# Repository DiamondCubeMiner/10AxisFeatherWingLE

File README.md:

# 10AxisFeatherWingLE #
A 10-DOF Featherwing, powered by LSM9DS1 and BMP280.

## Description ##
This featherwing uses I2C to connect both the IMU (LSM9DS1) and the altimeter (BMP280) to the Feather.
I made this to design projects that require a 10-DOF IMU in a tiny package where breakouts can affect the weight a lot and may not be a good option, such as a quadcopter, a model plane, or a model rocket.

## Drivers ##
These drivers should work as the project is a derivative of SparkFun hardware:
  - [SparkFun_LSM9DS1_Arduino_Library](https://github.com/sparkfun/SparkFun_LSM9DS1_Arduino_Library)
  - [SparkFun_BME280_Arduino_Library](https://github.com/sparkfun/SparkFun_BME280_Arduino_Library)

## Thanks ##
This project is derived from the following projects:
  - [SparkFun 9DoF Sensor Stick](https://github.com/sparkfun/9DOF_Sensor_Stick)
  - [SparkFun Atmospheric Sensor Breakout - BME280 (Qwiic)](https://github.com/sparkfun/Qwiic_Atmospheric_Sensor_Breakout_BME280)

Thanks to Sparkfun for their open-source schematics and libraries!

## License ##
This work is licensed under the Creative Commons Attribution-ShareAlike 4.0 International License. To view a copy of this license, visit http://creativecommons.org/licenses/by-sa/4.0/ or send a letter to Creative Commons, PO Box 1866, Mountain View, CA 94042, USA.

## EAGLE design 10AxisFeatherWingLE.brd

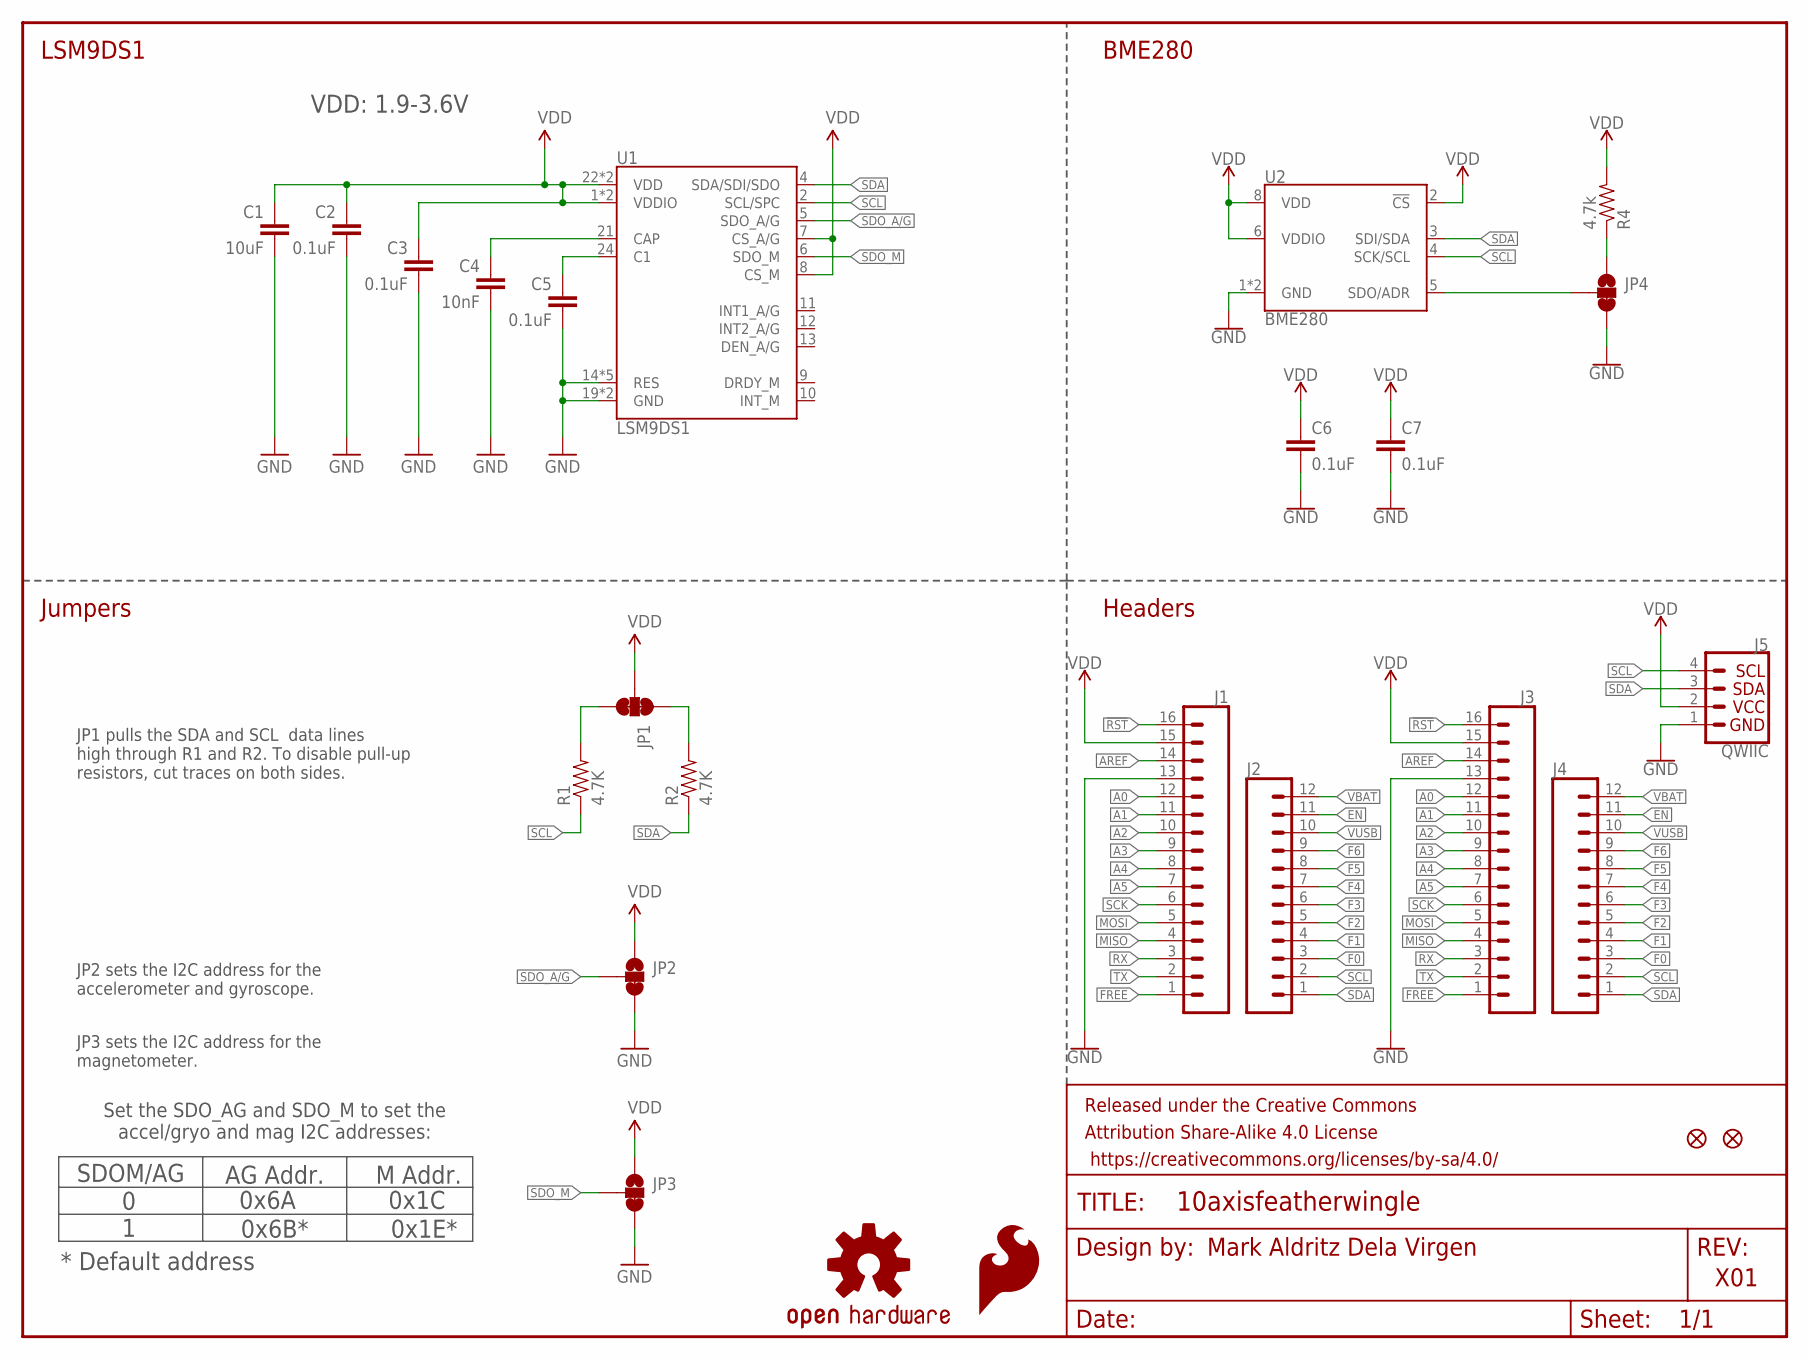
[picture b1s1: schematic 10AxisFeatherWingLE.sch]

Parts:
C1: 10uF; 0603-CAP@1
C2, C3, C5: 0.1uF; 0603-CAP@1
C4: 10nF; 0603-CAP@1
C6, C7: 0.1uF; 0603
FD3, FD4: FIDUCIALUFIDUCIAL; MICRO-FIDUCIAL
FRAME1: FRAME-LETTER; CREATIVE_COMMONS
J1, J3: CONN_161X16_NO_SILK; 1X16_NO_SILK
J2, J4: CONN_12NO_SILK; 1X12_NO_SILK
J5: QWIIC; 1X04_1MM_RA
JP1: JUMPER-SMT_3_2-NC_TRACE_SILK; SMT-JUMPER_3_2-NC_TRACE_SILK
JP2, JP3, JP4: JUMPER-SMT_3_1-NC_TRACE_SILK; SMT-JUMPER_3_1-NC_TRACE_SILK
LOGO1: SFE_LOGO_FLAME.1_INCH; SFE_LOGO_FLAME_.1
LOGO3: OSHW-LOGOMINI; OSHW-LOGO-MINI
R1, R2: 4.7K; 0603-RES
R4: 4.7k; 0603
U1: LSM9DS1; LGA24-8X4
U2: BME280; LGA-8-2.5X2.5

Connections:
!RST: J1.16, J3.16
A0: J1.12, J3.12
A1: J1.11, J3.11
A2: J1.10, J3.10
A3: J1.9, J3.9
A4: J1.8, J3.8
A5: J1.7, J3.7
AREF: J1.14, J3.14
EN: J2.11, J4.11
F0: J2.3, J4.3
F1: J2.4, J4.4
F2: J2.5, J4.5
F3: J2.6, J4.6
F4: J2.7, J4.7
F5: J2.8, J4.8
F6: J2.9, J4.9
FREE: J1.1, J3.1
GND: C1.2, C2.2, C3.2, C4.2, C5.2, C6.2, C7.2, J1.13, J3.13, J5.1, JP2.3, JP3.3, JP4.3, U1.14 (RES), U1.15 (RES), U1.16 (RES), U1.17 (RES), U1.18 (RES), U1.19 (GND), U1.20 (GND), U2.1 (GND), U2.7 (GND)
MISO: J1.4, J3.4
MOSI: J1.5, J3.5
unnamed: JP1.1, R2.2
unnamed: JP1.3, R1.2
unnamed: JP4.1, R4.1
unnamed: C4.1, U1.21 (CAP)
unnamed: C5.1, U1.24 (C1)
RX: J1.3, J3.3
SCK: J1.6, J3.6
SCL: J2.2, J4.2, J5.4, R1.1, U1.2 (SCL/SPC), U2.4 (SCK/SCL)
SDA: J2.1, J4.1, J5.3, R2.1, U1.4 (SDA/SDI/SDO), U2.3 (SDI/SDA)
SDO: JP4.2, U2.5 (SDO/ADR)
SDO_A/G: JP2.2, U1.5 (SDO_A/G)
SDO_M: JP3.2, U1.6 (SDO_M)
TX: J1.2, J3.2
VBAT: J2.12, J4.12
VDD: C1.1, C2.1, C3.1, C6.1, C7.1, J1.15, J3.15, J5.2, JP1.2, JP2.1, JP3.1, R4.2, U1.1 (VDDIO), U1.3 (VDDIO), U1.7 (CS_A/G), U1.8 (CS_M), U1.22 (VDD), U1.23 (VDD), U2.2 (!CS), U2.6 (VDDIO), U2.8 (VDD)
VUSB: J2.10, J4.10

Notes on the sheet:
Mark Aldritz Dela Virgen
X01
LSM9DS1
SDOM/AG
AG Addr.
0 1
M Addr.
Set the SDO_AG and SDO_M to set the accel/gryo and mag I2C addresses:
BME280
Headers
Jumpers
JP1 pulls the SDA and SCL data lines high through R1 and R2. To disable pull-up resistors, cut traces on both sides.
JP2 sets the I2C address for the accelerometer and gyroscope.
JP3 sets the I2C address for the magnetometer.
0x6A
0x6B*
0x1C
0x1E*
* Default address
VDD: 1.9-3.6V

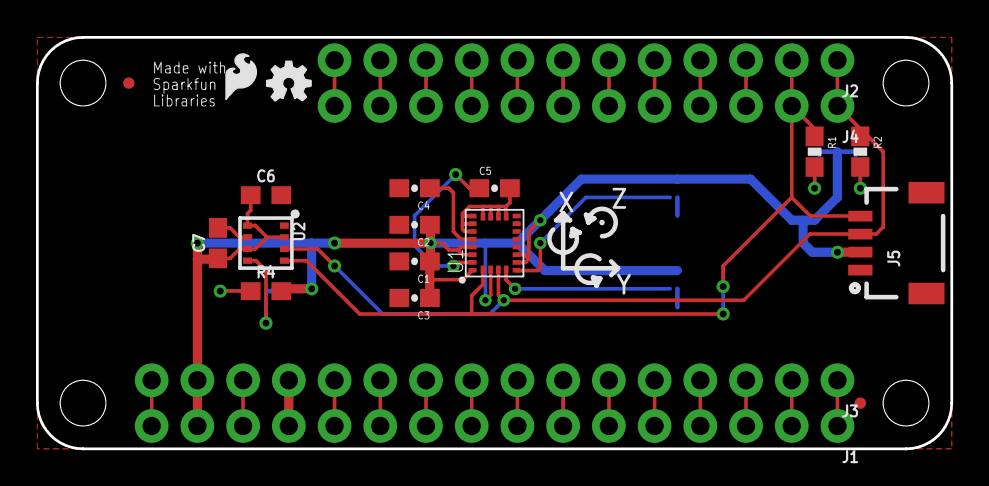
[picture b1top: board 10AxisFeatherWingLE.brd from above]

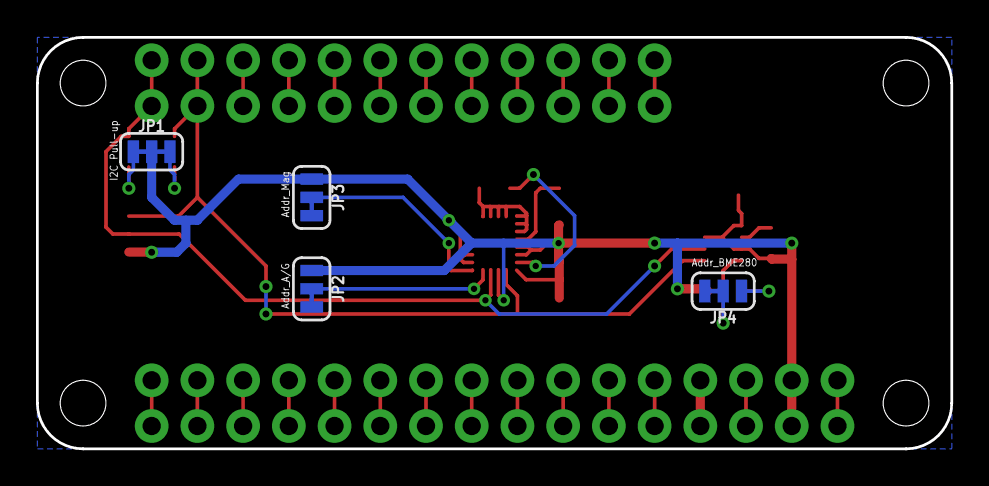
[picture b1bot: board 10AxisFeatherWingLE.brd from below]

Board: 2 copper layers, 50.8 x 22.9 mm, 26 parts (4 on the bottom side), 36 nets.

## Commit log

2019-12-22 Initial upload
2019-12-24 Added new features
    Added breakouts and silk text.
2019-12-26 Board silk edit
2019-12-31 Migration to KiCad
2020-01-05 Corrected capacitor values
    CAP and C1 capacitors were flipped, fixed
2020-01-07 Minor format fix
2020-01-12 Increased trace width
2020-01-17 Changed grove connector to STEMMA
2020-02-06 Removed STEMMA connector
    STEMMA requires the use of a 3.3V to 5V level shifter and voltage regulator.
    The board does not support these features, so they were removed.
2020-11-18 Eagle Refactor
    Remade the project in EAGLE. Needs signal routing.
2021-01-26 Added traces
    Added traces to board file.

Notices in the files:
parts and their libraries:
SparkFun-Capacitors: Licensing: Creative Commons ShareAlike 4.0 International - https://creativecommons.org/licenses/by-sa/4.0
SparkFun-Aesthetics: Released under the Creative Commons Attribution Share-Alike 4.0 License
SparkFun-Aesthetics: https://creativecommons.org/licenses/by-sa/4.0
